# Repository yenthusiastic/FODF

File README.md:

## Documentation for Fundamentals of Digital Fabrication
### by Thi Yen Thu Nguyen, thi-yen-thu.nguyen@hsrw.org

This is course offered as an Elective for the Winter semester 2017/2018 in Hochschule Rhein-waal Kamp-Lintfort. 

The instructors are Daniele Ingrassia (FabLab's Employee), Prof. Dr. Karsten Nebe (FabLab's Director) and Ahmed Belal(student assistant).

All documentation of the course and information about myself can be found on the <a href="http://fablab.hochschule-rhein-waal.de/fundamentals/2017/Thu.Nguyen/">website</a>. 

# FODF

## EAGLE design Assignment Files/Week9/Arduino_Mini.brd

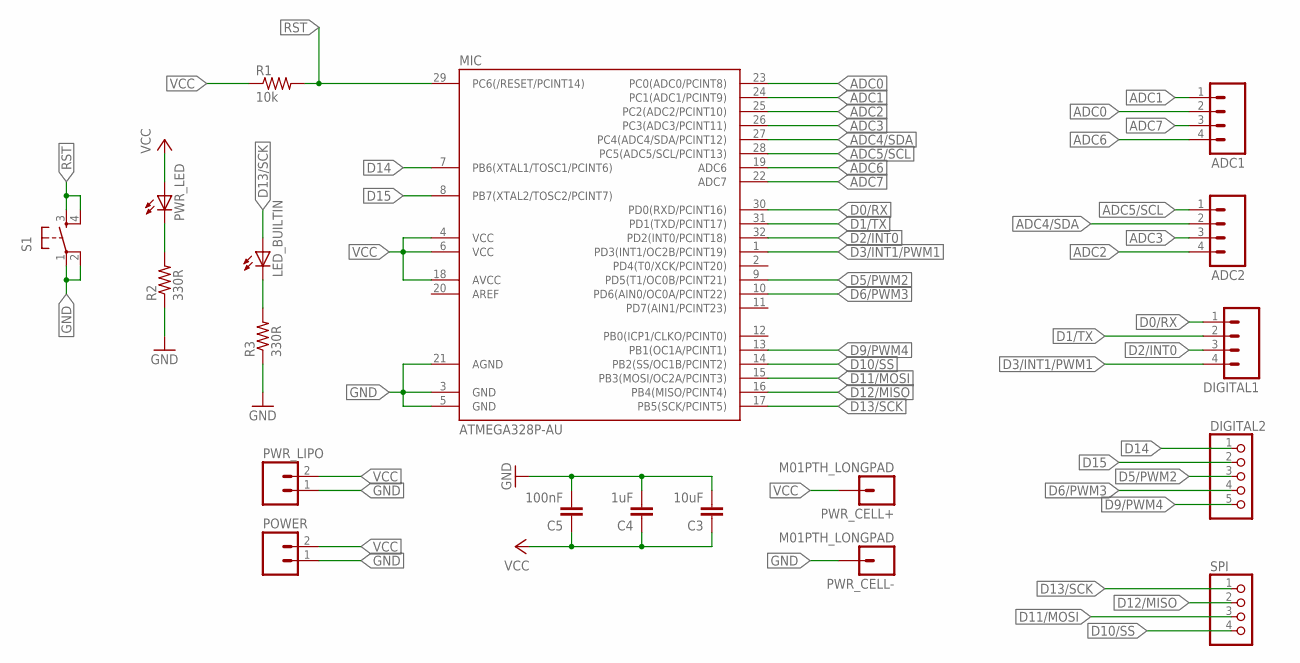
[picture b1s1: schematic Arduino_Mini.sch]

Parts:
ADC1, ADC2: M04LONGPADS; 1X04_LONGPADS
C3: 10uF; 1206
C4: 1uF; 1206
C5: 100nF; 1206
DIGITAL1: M04LONGPADS; 1X04_LONGPADS
DIGITAL2: PINHD-1X5; 1X05
LED_BUILTIN: LED1206; 1206
MIC: ATMEGA328P-AU; TQFP32-08
POWER: M02LOCK_LONGPADS; 1X02_LOCK_LONGPADS
PWR_CELL+: M01PTH_LONGPAD; 1X01_LONGPAD
PWR_CELL-: M01PTH_LONGPAD; 1X01_LONGPAD
PWR_LED: LED1206; 1206
PWR_LIPO: M02LOCK_LONGPADS; 1X02_LOCK_LONGPADS
R1: 10k; 1206
R2, R3: 330R; 1206
S1: 6MM_SWITCH6MM_SWITCH; 6MM_SWITCH
SPI: PINHD-1X4; 1X04

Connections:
ADC0: ADC1.2, MIC.23 (PC0(ADC0/PCINT8))
ADC1: ADC1.1, MIC.24 (PC1(ADC1/PCINT9))
ADC2: ADC2.4, MIC.25 (PC2(ADC2/PCINT10))
ADC3: ADC2.3, MIC.26 (PC3(ADC3/PCINT11))
ADC4/SDA: ADC2.2, MIC.27 (PC4(ADC4/SDA/PCINT12))
ADC5/SCL: ADC2.1, MIC.28 (PC5(ADC5/SCL/PCINT13))
ADC6: ADC1.4, MIC.19 (ADC6)
ADC7: ADC1.3, MIC.22 (ADC7)
D0/RX: DIGITAL1.1, MIC.30 (PD0(RXD/PCINT16))
D1/TX: DIGITAL1.2, MIC.31 (PD1(TXD/PCINT17))
D2/INT0: DIGITAL1.3, MIC.32 (PD2(INT0/PCINT18))
D3/INT1/PWM1: DIGITAL1.4, MIC.1 (PD3(INT1/OC2B/PCINT19))
D5/PWM2: DIGITAL2.3, MIC.9 (PD5(T1/OC0B/PCINT21))
D6/PWM3: DIGITAL2.4, MIC.10 (PD6(AIN0/OC0A/PCINT22))
D9/PWM4: DIGITAL2.5, MIC.13 (PB1(OC1A/PCINT1))
D10/SS: MIC.14 (PB2(SS/OC1B/PCINT2)), SPI.4
D11/MOSI: MIC.15 (PB3(MOSI/OC2A/PCINT3)), SPI.3
D12/MISO: MIC.16 (PB4(MISO/PCINT4)), SPI.2
D13/SCK: LED_BUILTIN.1 (A), MIC.17 (PB5(SCK/PCINT5)), SPI.1
D14: DIGITAL2.1, MIC.7 (PB6(XTAL1/TOSC1/PCINT6))
D15: DIGITAL2.2, MIC.8 (PB7(XTAL2/TOSC2/PCINT7))
GND: C3.2, C4.2, C5.2, MIC.3 (GND), MIC.5 (GND), MIC.21 (AGND), POWER.1, PWR_CELL-.1, PWR_LIPO.1, R2.1, R3.1, S1.1, S1.2 (P1)
unnamed: LED_BUILTIN.2 (C), R3.2
unnamed: PWR_LED.2 (C), R2.2
RST: MIC.29 (PC6(/RESET/PCINT14)), R1.2, S1.3 (S), S1.4 (S1)
VCC: C3.1, C4.1, C5.1, MIC.4 (VCC), MIC.6 (VCC), MIC.18 (AVCC), POWER.2, PWR_CELL+.1, PWR_LED.1 (A), PWR_LIPO.2, R1.1

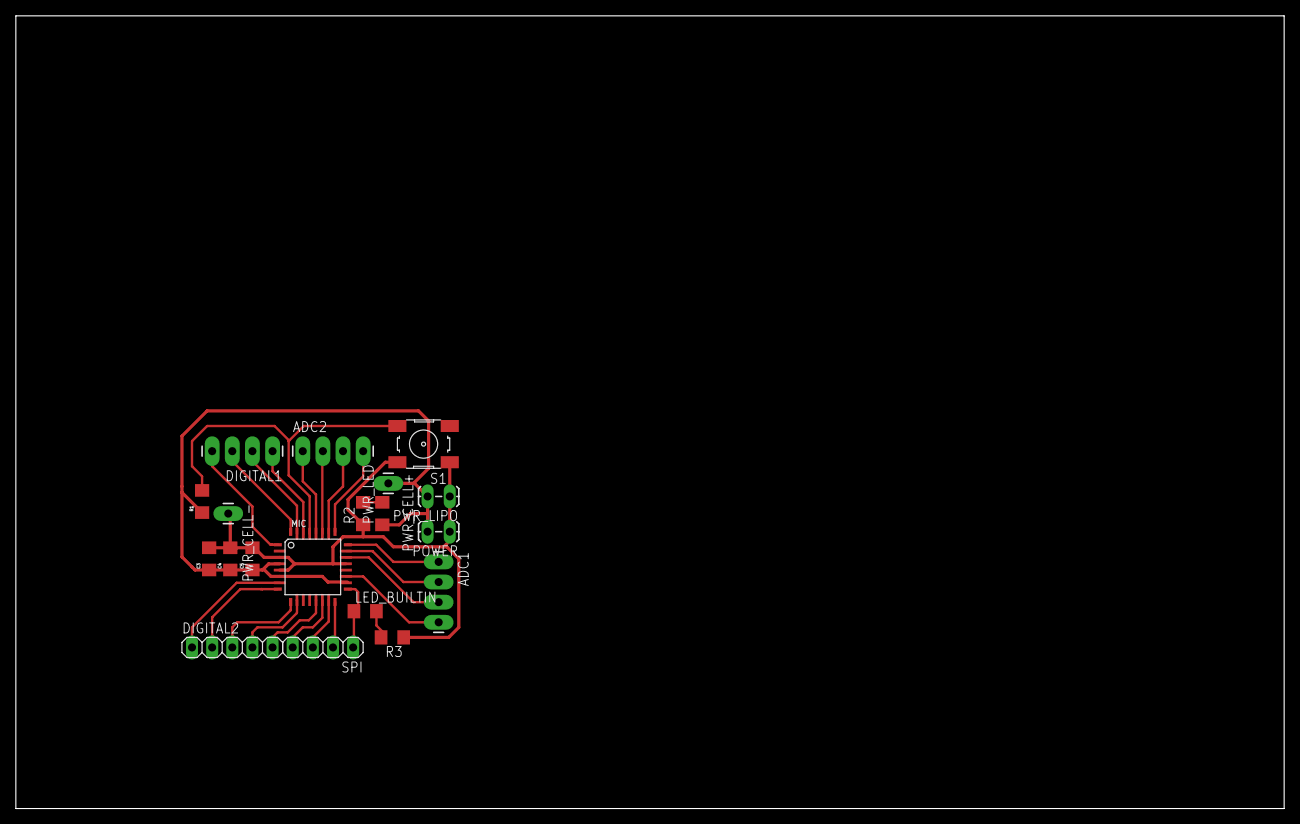
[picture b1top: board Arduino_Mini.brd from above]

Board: 2 copper layers, 160.0 x 100.0 mm, 19 parts (0 on the bottom side), 26 nets.

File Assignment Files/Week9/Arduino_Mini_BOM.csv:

"Part";"Value";"Device";"Package";"Description";"";
"ADC1";"";"M04LONGPADS";"1X04_LONGPADS";"Header 4";"";
"ADC2";"";"M04LONGPADS";"1X04_LONGPADS";"Header 4";"";
"C3";"10uF";"CAP1206";"1206";"Capacitor";"";
"C4";"1uF";"CAP1206";"1206";"Capacitor";"";
"C5";"100nF";"CAP1206";"1206";"Capacitor";"";
"DIGITAL1";"";"M04LONGPADS";"1X04_LONGPADS";"Header 4";"";
"DIGITAL2";"";"PINHD-1X5";"1X05";"PIN HEADER";"";
"LED_BUILTIN";"";"LED1206";"1206";"GREEN";"";
"MIC";"ATMEGA328P-AU";"ATMEGA48/88/168-AU";"TQFP32-08";"";"";
"POWER";"";"M02LOCK_LONGPADS";"1X02_LOCK_LONGPADS";"Header 2";"";
"PWR_LED";"";"LED1206";"1206";"RED";"";
"PWR_LIPO";"";"CONN_HEADER_PH_2POS";"2POS_TOP_2MM";"JST Header";"";
"R1";"10k";"RESISTOR1206";"1206";"Resistor";"";
"R2";"330R";"RESISTOR1206";"1206";"";"";
"R3";"330R";"RESISTOR1206";"1206";"";"";
"S1";"";"6MM_SWITCH6MM_SWITCH";"6MM_SWITCH";"OMRON SWITCH";"";
"SPI";"";"PINHD-1X4";"1X04";"PIN HEADER";"";

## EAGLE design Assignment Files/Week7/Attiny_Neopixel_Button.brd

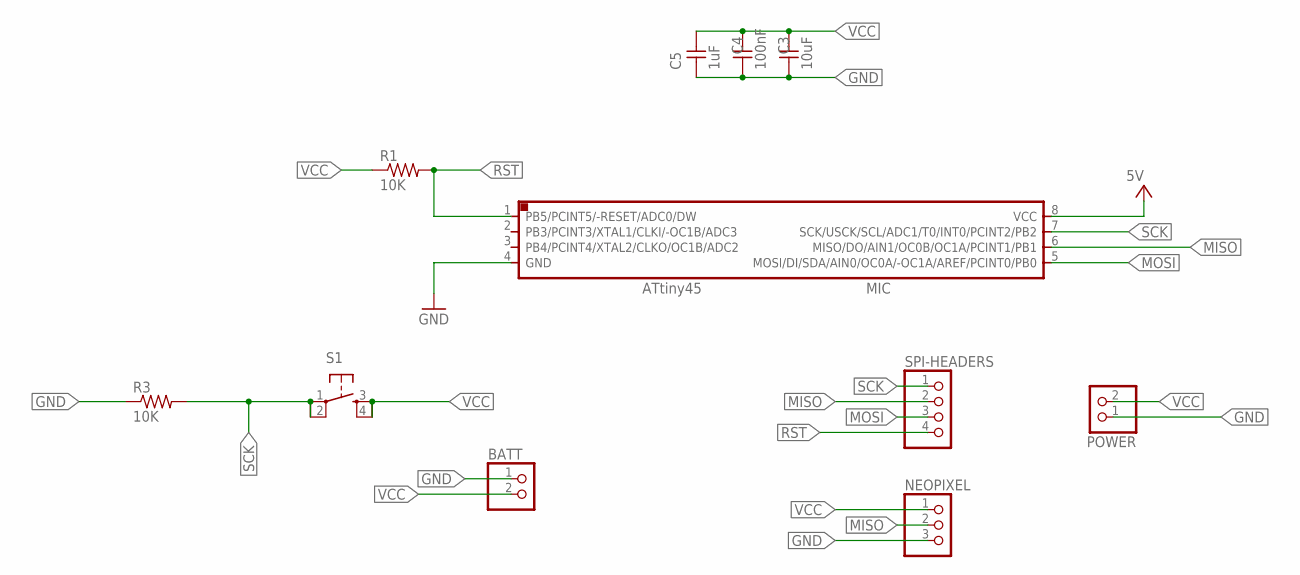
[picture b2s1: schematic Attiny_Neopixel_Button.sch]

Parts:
BATT: PINHD-1X2; 1X02
C3: 10uF; 1206
C4: 100nF; 1206
C5: 1uF; 1206
MIC: ATTINY45SI; SOIC8
NEOPIXEL: PINHD-1X3; 1X03
POWER: PINHD-1X2; 1X02
R1, R3: 10K; 1206
S1: 6MM_SWITCH6MM_SWITCH; 6MM_SWITCH
SPI-HEADERS: PINHD-1X4; 1X04

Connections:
GND: BATT.1, C3.1, C4.1, C5.1, MIC.4 (GND), NEOPIXEL.3, POWER.1, R3.1
MISO: MIC.6 (MISO/DO/AIN1/OC0B/OC1A/PCINT1/PB1), NEOPIXEL.2, SPI-HEADERS.2
MOSI: MIC.5 (MOSI/DI/SDA/AIN0/OC0A/-OC1A/AREF/PCINT0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), SPI-HEADERS.3
RST: MIC.1 (PB5/PCINT5/-RESET/ADC0/DW), R1.2, SPI-HEADERS.4
SCK: MIC.7 (SCK/USCK/SCL/ADC1/T0/INT0/PCINT2/PB2), R3.2, S1.1, S1.2 (P1), SPI-HEADERS.1
VCC: BATT.2, C3.2, C4.2, C5.2, MIC.8 (VCC), NEOPIXEL.1, POWER.2, R1.1, S1.3 (S), S1.4 (S1)

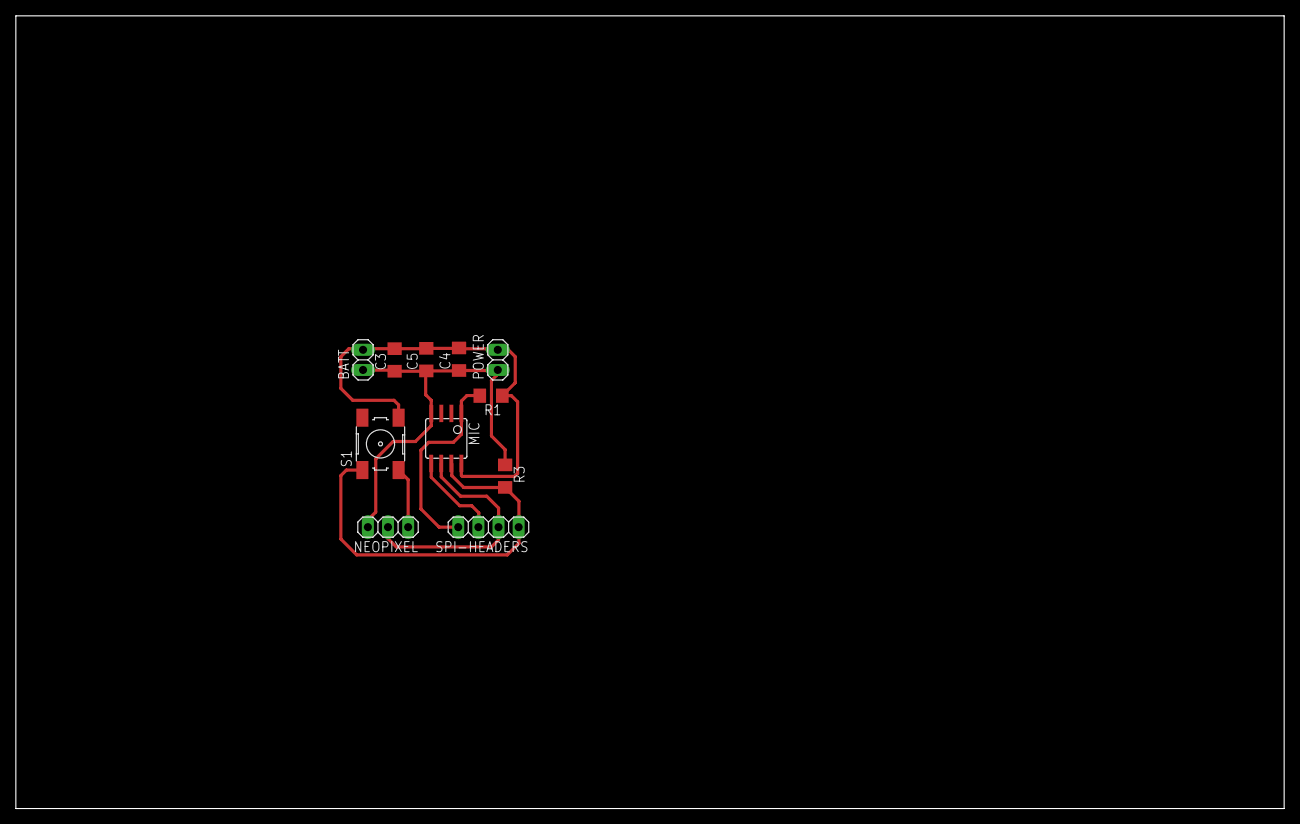
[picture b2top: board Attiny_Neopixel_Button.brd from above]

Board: 2 copper layers, 160.0 x 100.0 mm, 11 parts (0 on the bottom side), 6 nets.

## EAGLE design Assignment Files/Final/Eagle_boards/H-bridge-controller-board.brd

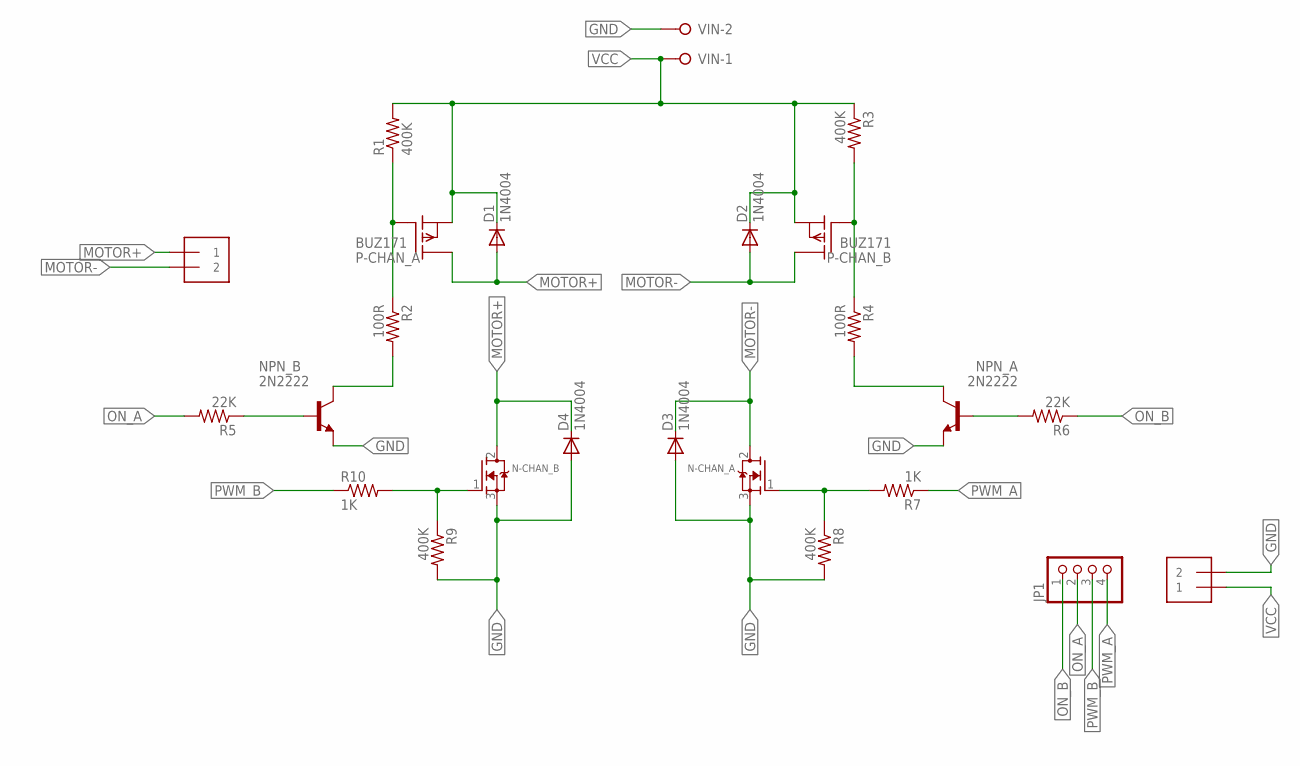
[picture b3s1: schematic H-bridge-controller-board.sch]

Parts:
D1, D2, D3, D4: 1N4004; DO41-10
JP1: PINHD-1X4; 1X04
MOTOR_IN: 1X2-3.5MM
N-CHAN_A: MOSFET-NGDS_TO220V; TO220V
N-CHAN_B: MOSFET-NGDS_TO220V; TO220V
NPN_A: 2N2222; TO92-EBC-OVAL
NPN_B: 2N2222; TO92-EBC-OVAL
P-CHAN_A: BUZ171; TO220
P-CHAN_B: BUZ171; TO220
R1, R3, R8, R9: 400K; R1206FAB
R2, R4: 100R; R1206FAB
R5, R6: 22K; R1206FAB
R7, R10: 1K; R1206FAB
VIN: W237-02P; W237-132
VOUT: 1X2-3.5MM

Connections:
GND: D3.A, D4.A, N-CHAN_A.3 (S), N-CHAN_B.3 (S), NPN_A.E, NPN_B.E, R8.2, R9.2, VIN.2, VOUT.2
MOTOR+: D1.A, D4.C, MOTOR_IN.1, N-CHAN_B.2 (D), P-CHAN_A.2 (D)
MOTOR-: D2.A, D3.C, MOTOR_IN.2, N-CHAN_A.2 (D), P-CHAN_B.2 (D)
unnamed: P-CHAN_A.1 (G), R1.1, R2.1
unnamed: P-CHAN_B.1 (G), R3.2, R4.1
unnamed: NPN_B.C, R2.2
unnamed: NPN_B.B, R5.1
unnamed: NPN_A.C, R4.2
unnamed: NPN_A.B, R6.2
unnamed: N-CHAN_B.1 (G), R9.1, R10.2
unnamed: N-CHAN_A.1 (G), R7.2, R8.1
ON_A: JP1.2, R5.2
ON_B: JP1.1, R6.1
PWM_A: JP1.4, R7.1
PWM_B: JP1.3, R10.1
VCC: D1.C, D2.C, P-CHAN_A.3 (S), P-CHAN_B.3 (S), R1.2, R3.1, VIN.1, VOUT.1

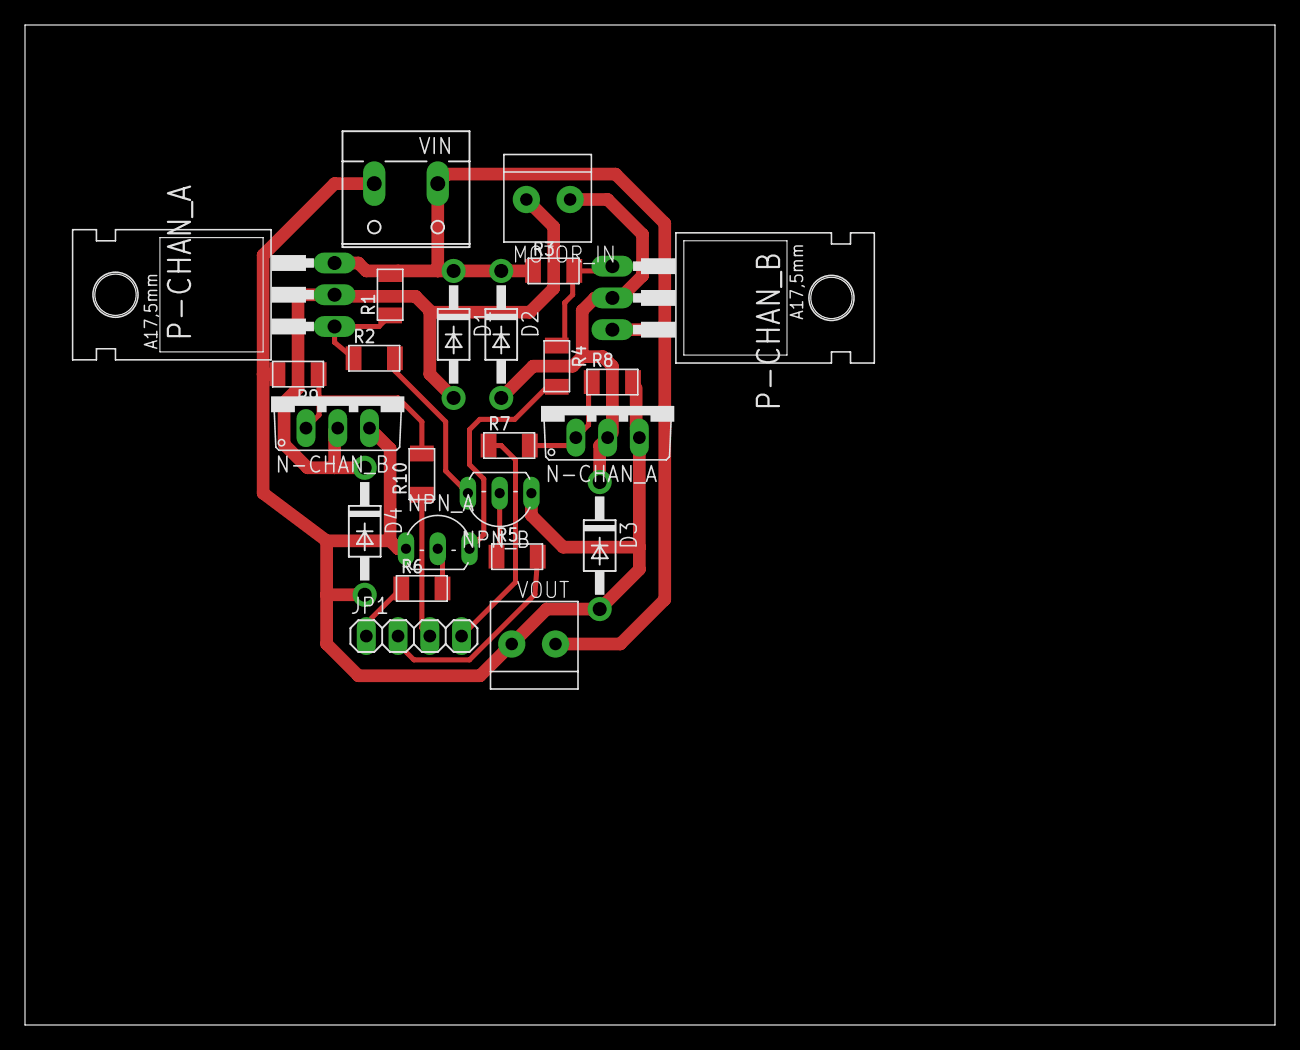
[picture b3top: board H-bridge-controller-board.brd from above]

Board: 2 copper layers, 100.0 x 80.0 mm, 24 parts (0 on the bottom side), 16 nets.

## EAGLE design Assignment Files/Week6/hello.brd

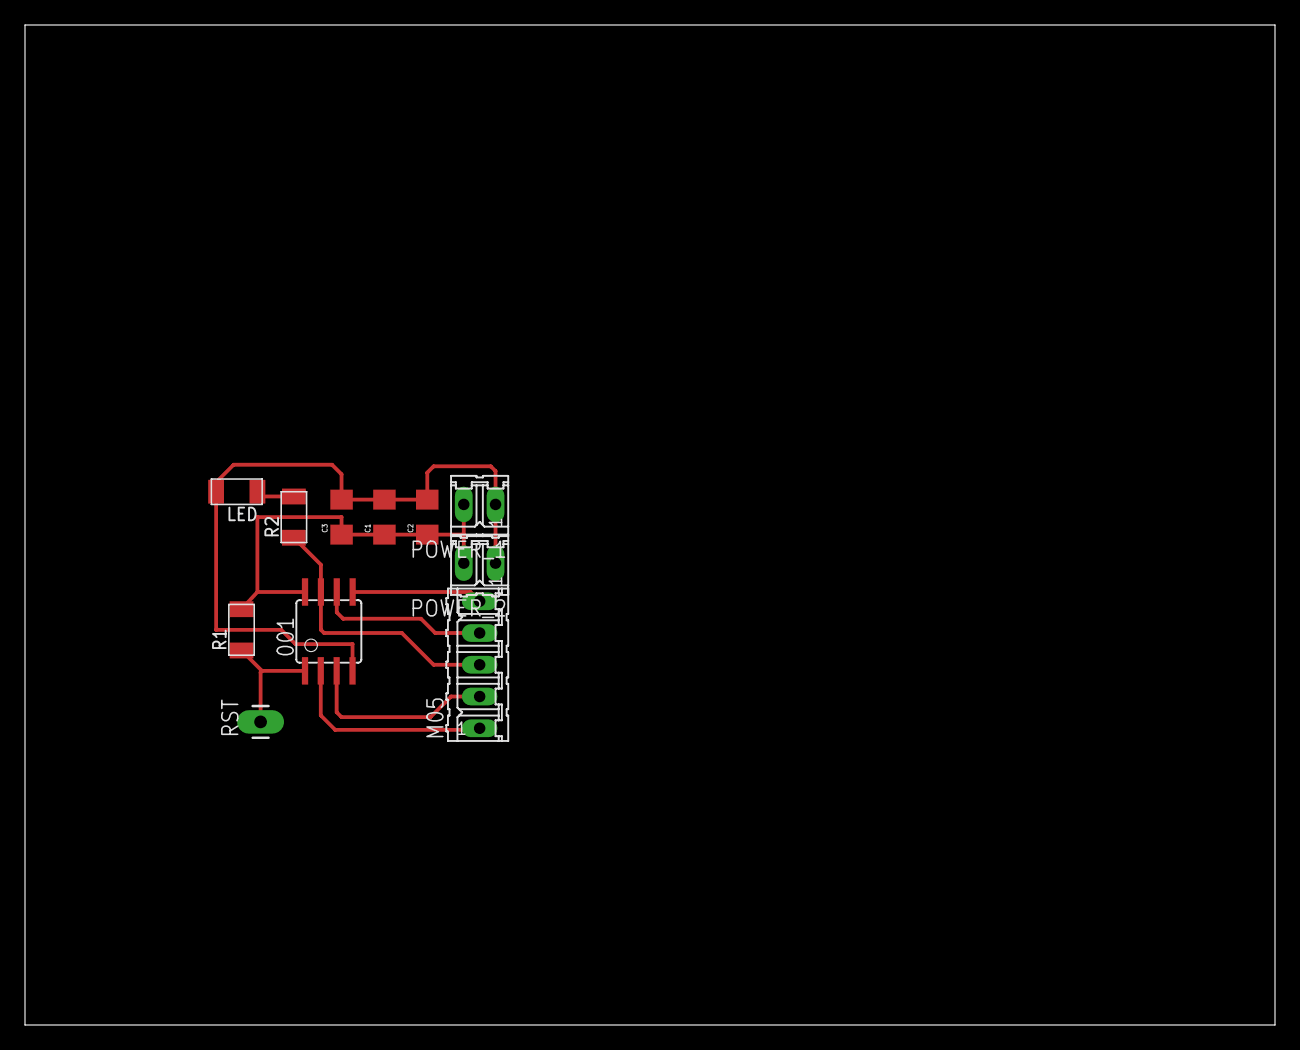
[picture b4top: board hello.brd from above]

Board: 2 copper layers, 100.0 x 80.0 mm, 11 parts (0 on the bottom side), 9 nets.

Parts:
001: ATTINY45SI; SOIC8
C1: 1uF; 1206
C2: 10uF; 1206
C3: 100nF; 1206
LED: YELLOW; LED1206FAB
M05: 05P
POWER_1, POWER_2: 02P
R1: 10K; R1206FAB
R2: 499; R1206FAB
RST: M01; 1X01_LONGPAD

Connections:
ADC2: 001.3, M05.2
ADC3: 001.2, M05.1
GND: 001.4, C1.2, C2.2, C3.2, LED.2, POWER_1.1, POWER_2.1
MISO: 001.6, M05.4
MOSI: 001.5, M05.5
unnamed: LED.1, R2.2
RST: 001.1, R1.1, RST.1
SCK: 001.7, M05.3, R2.1
VCC: 001.8, C1.1, C2.1, C3.1, POWER_1.2, POWER_2.2, R1.2

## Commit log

2018-06-21 Create CNAME
2018-10-10 added mailto: link for email in about.html
2019-02-13 Update CNAME

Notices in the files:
parts and their libraries:
01_SparkFun: Licensing: CC v3.0 Share-Alike You are welcome to use this library for commercial purposes.
